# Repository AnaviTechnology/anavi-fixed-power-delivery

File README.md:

# ANAVI Fixed Power Delivery

Small 2-layer fixed USB-C PD power sink with [CYPD3177](https://www.infineon.com/cms/en/product/universal-serial-bus/usb-c-charging-port-controllers/ez-pd-barrel-connector-replacement-bcr/cypd3177-24lqxq/) and 2 pin terminal block.

The board provides a fixed output from USB-C PD (Power Delivery) using the CYPD3177 chipset. It's highly flexible, allowing USB-C Charging up to 15W and USB-C PD up to 100W. Unlike many other chips available, it does not require any firmware nor flashing, and power settings are configured with pullup and pulldown resistors. This design is inspired by [CYPD3177-Breakout](https://github.com/Hugoyhu/CYPD3177-Breakout). Resistors R1 and R2 set the maximum current, which is 2A according to the default values in the schematics. By adjusting the values of resistors R3, R4, R8, and R9, the board can be configured to a fixed output voltage of 5V, 9V, 12V, 15V, or 20V.

# License

The project is released under the [Creative Commons Attribution-ShareAlike 4.0 International (CC BY-SA 4.0)](https://creativecommons.org/licenses/by-sa/4.0/).

Note: This is a human-readable summary of (and not a substitute for) the [license](https://creativecommons.org/licenses/by-sa/4.0/legalcode).

You are free to:

Share — copy and redistribute the material in any medium or format Adapt — remix, transform, and build upon the material for any purpose, even commercially. The licensor cannot revoke these freedoms as long as you follow the license terms. Under the following terms:

Attribution — You must give appropriate credit, provide a link to the license, and indicate if changes were made. You may do so in any reasonable manner, but not in any way that suggests the licensor endorses you or your use. ShareAlike — If you remix, transform, or build upon the material, you must distribute your contributions under the same license as the original. No additional restrictions — You may not apply legal terms or technological measures that legally restrict others from doing anything the license permits. Notices:

You do not have to comply with the license for elements of the material in the public domain or where your use is permitted by an applicable exception or limitation. No warranties are given. The license may not give you all of the permissions necessary for your intended use. For example, other rights such as publicity, privacy, or moral rights may limit how you use the material.

You will have to provide a link to the original creator of the project http://www.anavi.technology on any documentation or website.

Credit can be attributed through a link to the creator website: http://www.anavi.technology

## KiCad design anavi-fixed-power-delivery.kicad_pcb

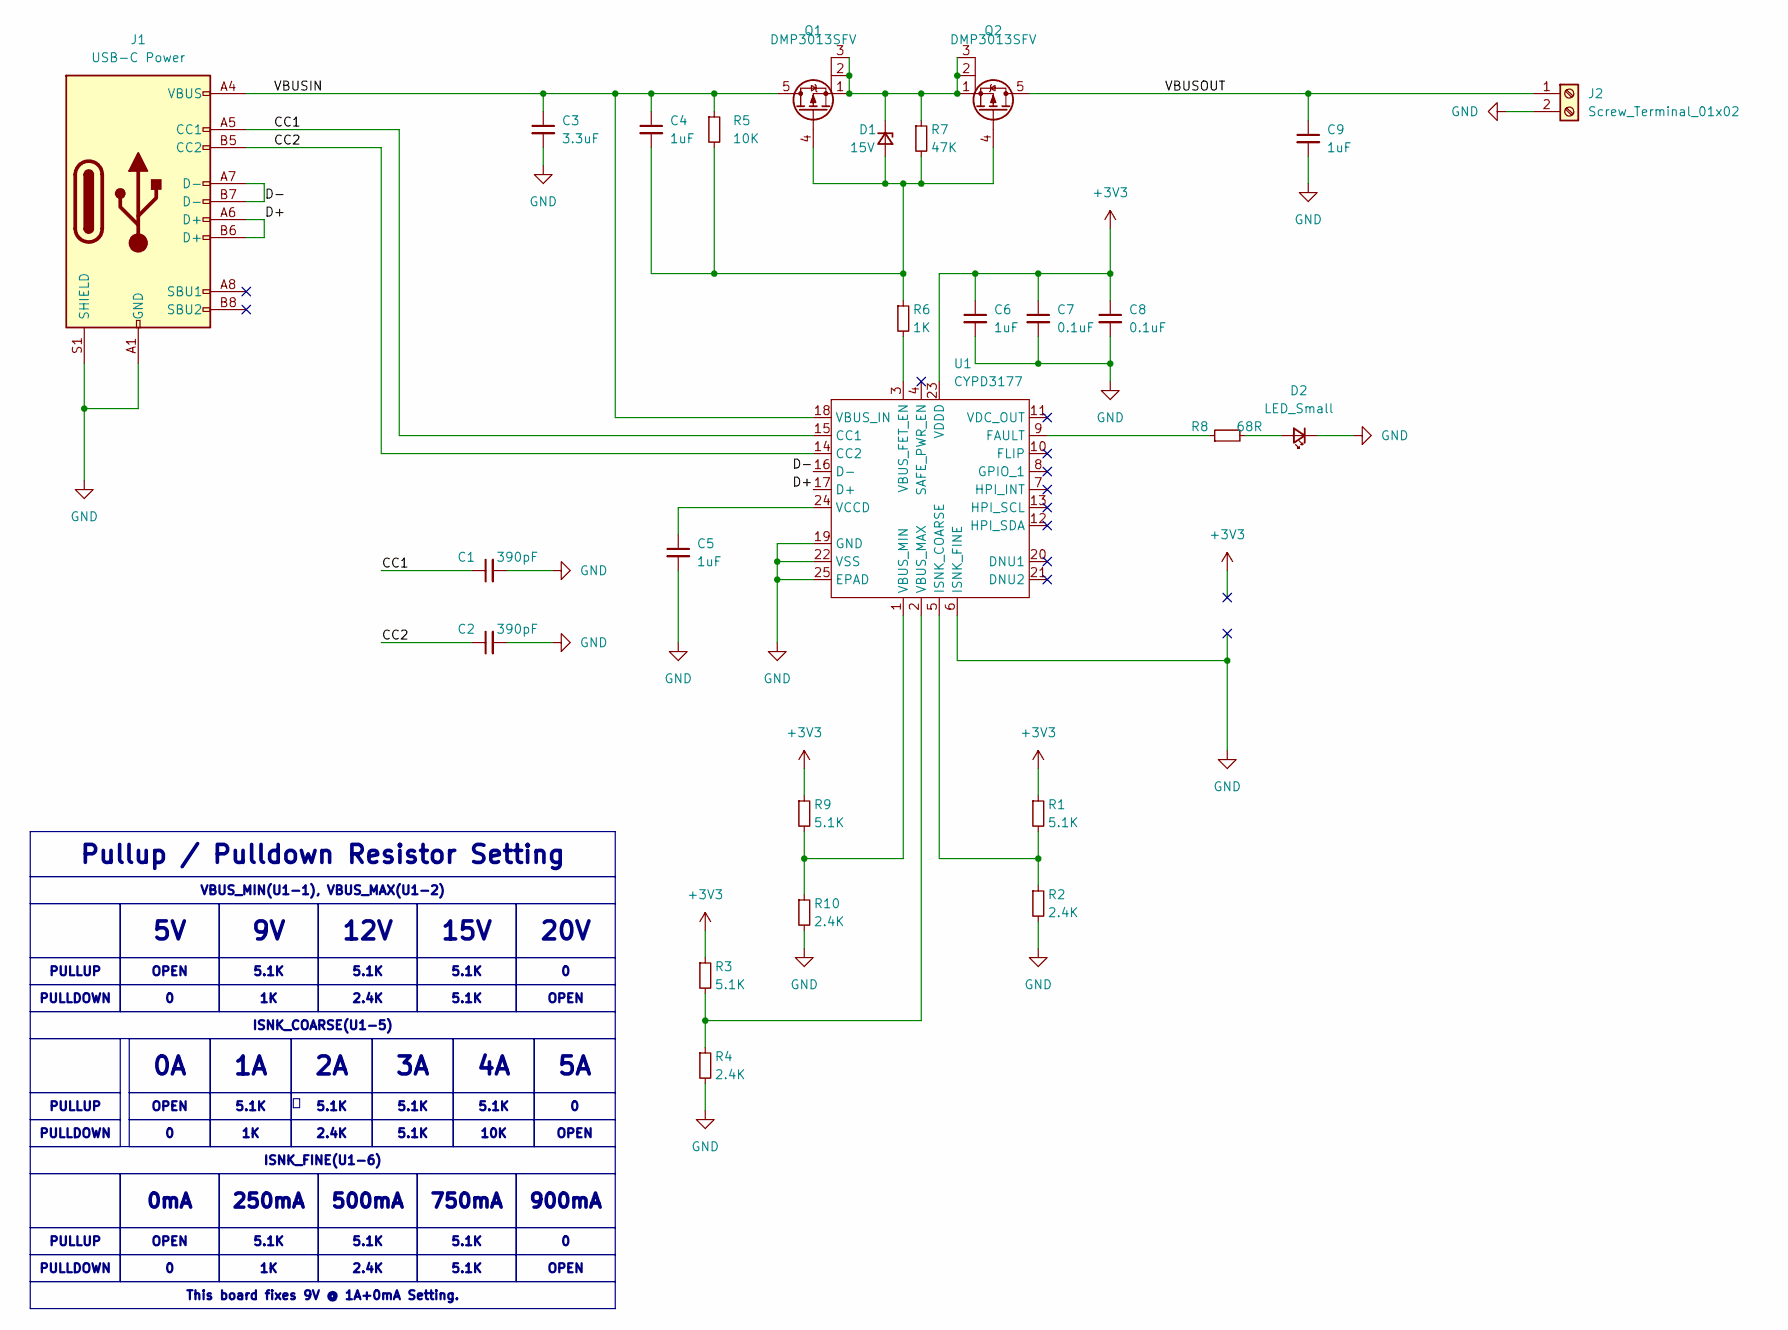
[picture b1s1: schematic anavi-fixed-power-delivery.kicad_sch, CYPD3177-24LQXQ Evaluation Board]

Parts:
C1, C2: 390pF; C_0603_1608Metric_Pad1.08x0.95mm_HandSolder
C3: 3.3uF; C_0805_2012Metric_Pad1.18x1.45mm_HandSolder
C4, C5, C6, C9: 1uF; C_0603_1608Metric_Pad1.08x0.95mm_HandSolder
C7, C8: 0.1uF; C_0603_1608Metric_Pad1.08x0.95mm_HandSolder
D1: 15V; D_SOD-323_HandSoldering
D2: LED_Small; LED_1206_3216Metric
J1: USB-C Power; USB_C_Receptacle_HRO_TYPE-C-31-M-12
J2: Screw_Terminal_01x02; TerminalBlock_Phoenix_MKDS-1,5-2_1x02_P5.00mm_Horizontal
Q1, Q2: DMP3013SFV; Diodes_PowerDI3333-8
R1, R3, R9: 5.1K; R_0603_1608Metric_Pad0.98x0.95mm_HandSolder
R2, R4, R10: 2.4K; R_0603_1608Metric_Pad0.98x0.95mm_HandSolder
R5: 10K; R_0603_1608Metric_Pad0.98x0.95mm_HandSolder
R6: 1K; R_0603_1608Metric_Pad0.98x0.95mm_HandSolder
R7: 47K; R_0603_1608Metric_Pad0.98x0.95mm_HandSolder
R8: 68R; R_0603_1608Metric_Pad0.98x0.95mm_HandSolder
U1: CYPD3177; QFN-24-1EP_4x4mm_P0.5mm_EP2.7x2.7mm

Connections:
+3V3: C6.1, C7.1, C8.1, R1.1, R3.1, R9.1, U1.23 (VDDD)
/CC1: C1.1, J1.A5 (CC1), U1.15 (CC1)
/CC2: C2.1, J1.B5 (CC2), U1.14 (CC2)
/D+: J1.A6 (D+), J1.B6 (D+), U1.17 (D+)
/D-: J1.A7 (D-), J1.B7 (D-), U1.16 (D-)
/VBUSIN: C3.1, C4.1, J1.A4 (VBUS), J1.A9 (VBUS), J1.B4 (VBUS), J1.B9 (VBUS), Q1.5 (D), R5.1, U1.18 (VBUS_IN)
/VBUSOUT: C9.1, J2.1, Q2.5 (D)
GND: C1.2, C2.2, C3.2, C5.2, C6.2, C7.2, C8.2, C9.2, D2.1 (K), J1.A1 (GND), J1.A12 (GND), J1.B1 (GND), J1.B12 (GND), J1.S1 (SHIELD), J2.2, R2.2, R4.2, R10.2, U1.6 (ISNK_FINE), U1.19 (GND), U1.22 (VSS), U1.25 (EPAD)
unnamed: C4.2, D1.2 (A), Q1.4 (G), Q2.4 (G), R5.2, R6.1, R7.2
unnamed: D1.1 (K), Q1.1 (S), Q1.2, Q1.3, Q2.1 (S), Q2.2, Q2.3, R7.1
unnamed: D2.2 (A), R8.2
unnamed: R8.1, U1.9 (FAULT)
unnamed: R1.2, R2.1, U1.5 (ISNK_COARSE)
unnamed: R6.2, U1.3 (VBUS_FET_EN)
unnamed: R3.2, R4.1, U1.2 (VBUS_MAX)
unnamed: R9.2, R10.1, U1.1 (VBUS_MIN)
unnamed: C5.1, U1.24 (VCCD)

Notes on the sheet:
20V
5.1K
ISNK_COARSE(U1-5)
2.4K
0mA
VBUS_MIN(U1-1), VBUS_MAX(U1-2)
500mA
OPEN
OPEN
10K
15V
This board fixes 9V @ 1A+0mA Setting.
PULLDOWN
12V
250mA
PULLUP
900mA
Pullup / Pulldown Resistor Setting
750mA
ISNK_FINE(U1-6)

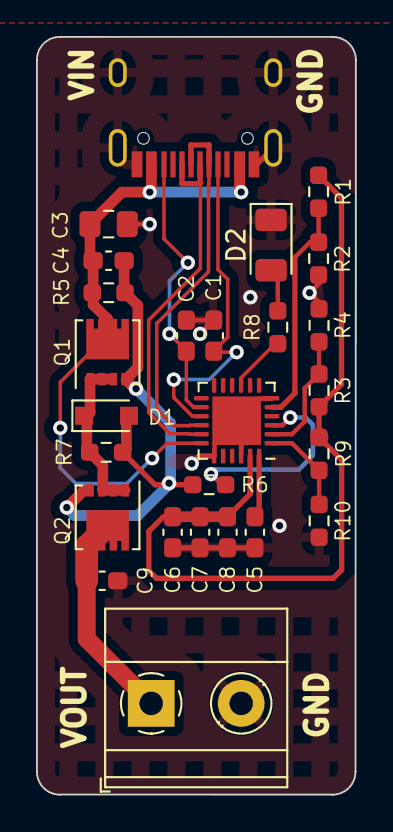
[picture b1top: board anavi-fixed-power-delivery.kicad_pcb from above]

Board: 2 copper layers, 17.7 x 42.1 mm, 26 parts (0 on the bottom side), 17 nets.

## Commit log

2024-07-18 Initial version of ANAVI Fixed Power Delivery
    Small 2-layer fixed USB-C PD power sink with CYPD3177 and 2 pin
    terminal block.
2024-07-22 Minor improvements

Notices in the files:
anavi-fixed-power-delivery.kicad_pcb:
(c) 2024 rev 1.0
